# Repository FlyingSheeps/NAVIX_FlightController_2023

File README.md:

# NAVIXフライトコントローラー(2023)

2023年のX-5 Leaderの飛行に使われていた制御系です．

## ソフトウェア
ソフトウェアはArduinoIDEで書き込むために書かれています．基本的に記述されているコメントを読めばわかるようになっています．

## ハードウェア
ハードウェアはESP32-WROOM-32EをMCUとして，
- PWM4系統
- SBUS用RX
- I2C
- 書き込み用シリアル
を備えています．

使用するパーツは基本的にすべて秋月電子通商で購入できます．詳細はFreeFlighter/FreeFlighter.csvのvalue列にある品名で検索すれば出てきます．

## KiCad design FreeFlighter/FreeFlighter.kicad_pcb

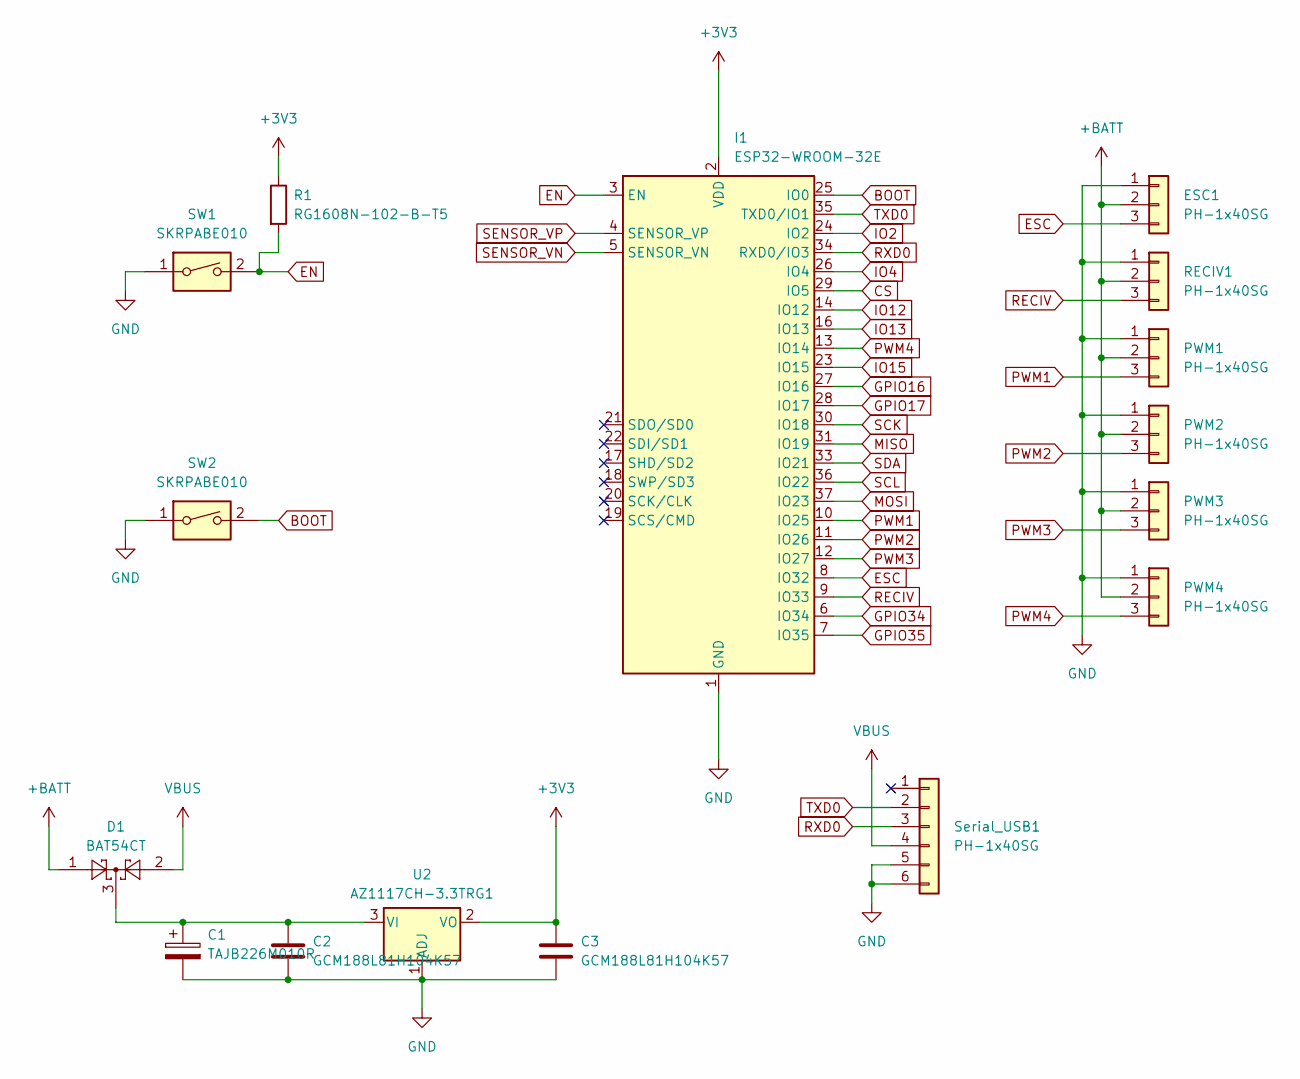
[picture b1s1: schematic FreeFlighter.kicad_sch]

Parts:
C1: TAJB226M010R; CP_EIA-3528-15_AVX-H
C2, C3: GCM188L81H104K57; C_0603_1608Metric
D1: BAT54CT; SOT-523
ESC1: PH-1x40SG; PinHeader_1x03_P2.54mm_Vertical
I1: ESP32-WROOM-32E; ESP32-WROOM-32
PWM1, PWM2, PWM3, PWM4: PH-1x40SG; PinHeader_1x03_P2.54mm_Vertical
R1: RG1608N-102-B-T5; R_0603_1608Metric
RECIV1: PH-1x40SG; PinHeader_1x03_P2.54mm_Vertical
SW1, SW2: SKRPABE010; SW_Push_1P1T_NO_Vertical_Wuerth_434133025816
Serial_USB1: PH-1x40SG; PinHeader_1x06_P2.54mm_Vertical
U2: AZ1117CH-3.3TRG1; SOT-223-3_TabPin2

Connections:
+3V3: C3.1, I1.2 (VDD), R1.1, U2.2 (VO)
+BATT: D1.1, ESC1.2, PWM1.2, PWM2.2, PWM3.2, PWM4.2, RECIV1.2
BOOT: I1.25 (IO0), SW2.2
CS: I1.29 (IO5)
EN: I1.3 (EN), R1.2, SW1.2
ESC: ESC1.3, I1.8 (IO32)
GND: C1.2, C2.2, C3.2, ESC1.1, I1.1 (GND), I1.15 (GND), I1.38 (GND), I1.39 (GND), PWM1.1, PWM2.1, PWM3.1, PWM4.1, RECIV1.1, SW1.1, SW2.1, Serial_USB1.5, Serial_USB1.6, U2.1 (ADJ)
GPIO16: I1.27 (IO16)
GPIO17: I1.28 (IO17)
GPIO34: I1.6 (IO34)
GPIO35: I1.7 (IO35)
IO2: I1.24 (IO2)
IO4: I1.26 (IO4)
IO12: I1.14 (IO12)
IO13: I1.16 (IO13)
IO15: I1.23 (IO15)
MISO: I1.31 (IO19)
MOSI: I1.37 (IO23)
unnamed: C1.1, C2.1, D1.3, U2.3 (VI)
PWM1: I1.10 (IO25), PWM1.3
PWM2: I1.11 (IO26), PWM2.3
PWM3: I1.12 (IO27), PWM3.3
PWM4: I1.13 (IO14), PWM4.3
RECIV: I1.9 (IO33), RECIV1.3
RXD0: I1.34 (RXD0/IO3), Serial_USB1.3
SCK: I1.30 (IO18)
SCL: I1.36 (IO22)
SDA: I1.33 (IO21)
SENSOR_VN: I1.5 (SENSOR_VN)
SENSOR_VP: I1.4 (SENSOR_VP)
TXD0: I1.35 (TXD0/IO1), Serial_USB1.2
VBUS: D1.2, Serial_USB1.4

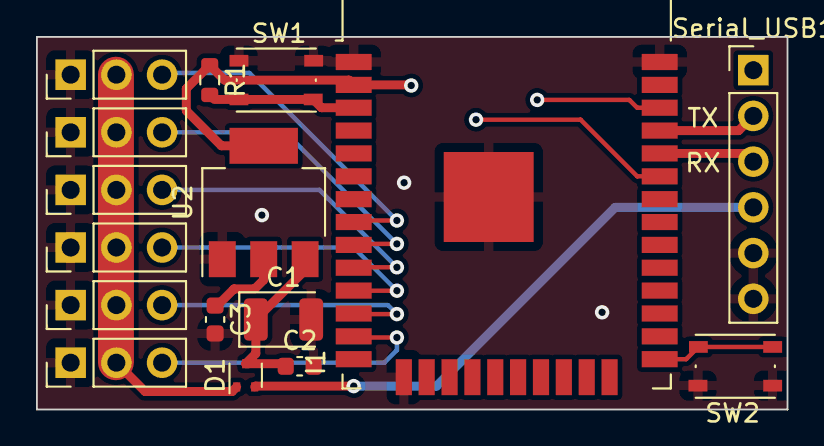
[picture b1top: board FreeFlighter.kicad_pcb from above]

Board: 2 copper layers, 41.7 x 20.7 mm, 16 parts (0 on the bottom side), 15 nets.

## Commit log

2023-11-04 init
2023-11-04 readme
2023-11-11 制御修正
